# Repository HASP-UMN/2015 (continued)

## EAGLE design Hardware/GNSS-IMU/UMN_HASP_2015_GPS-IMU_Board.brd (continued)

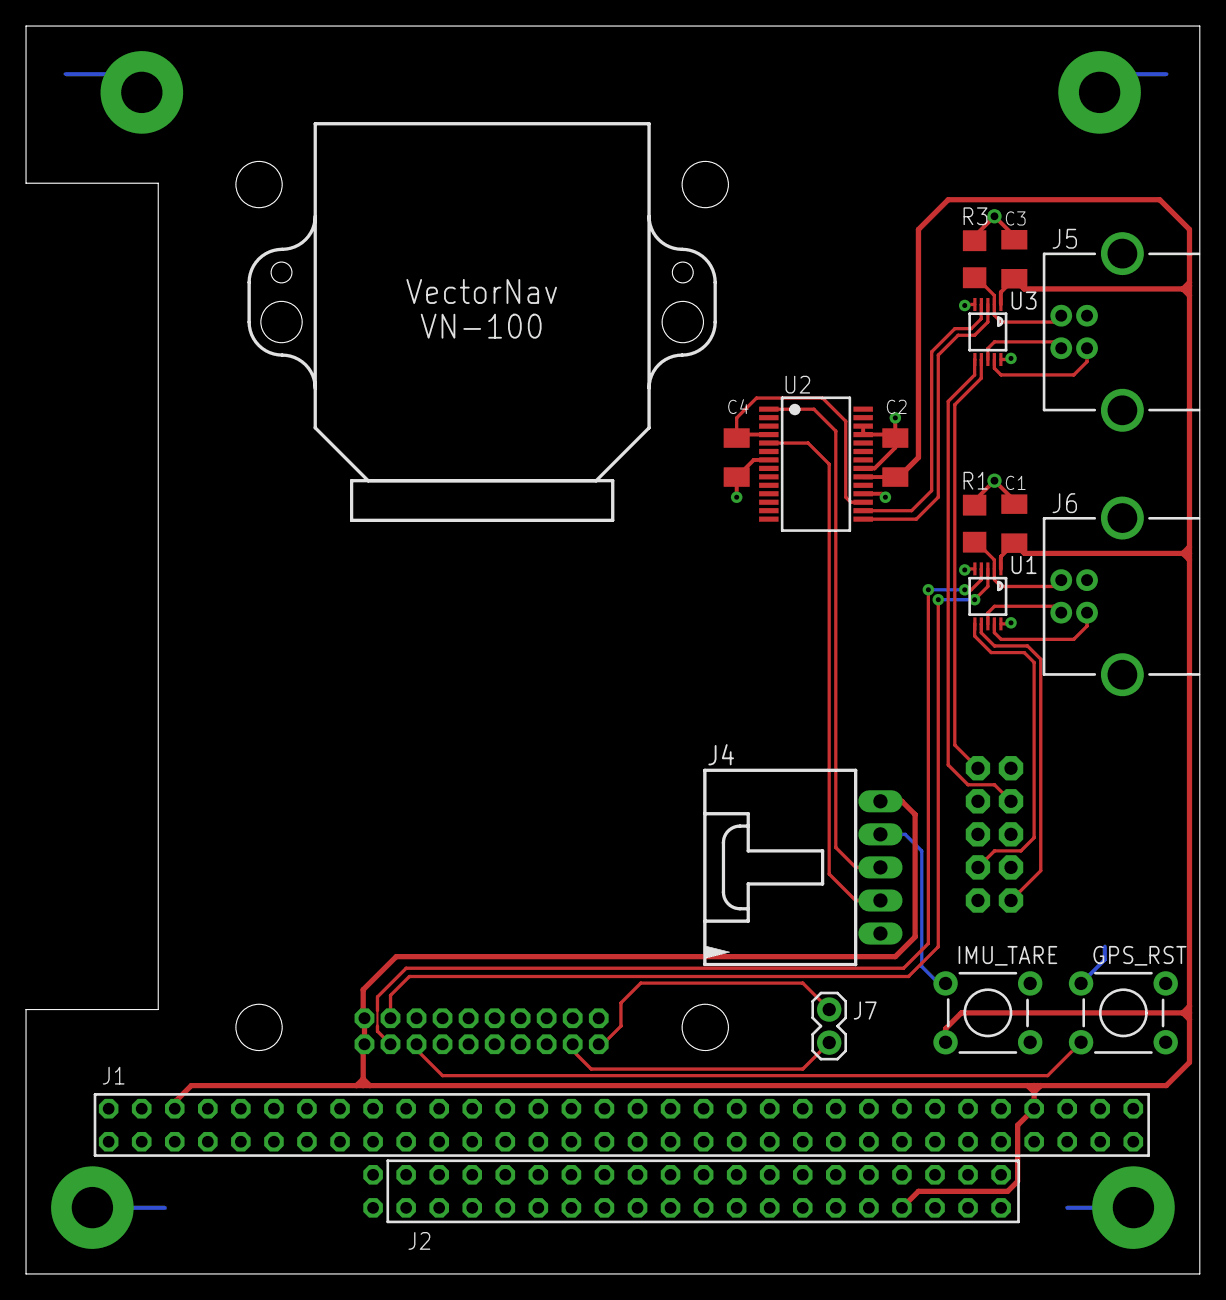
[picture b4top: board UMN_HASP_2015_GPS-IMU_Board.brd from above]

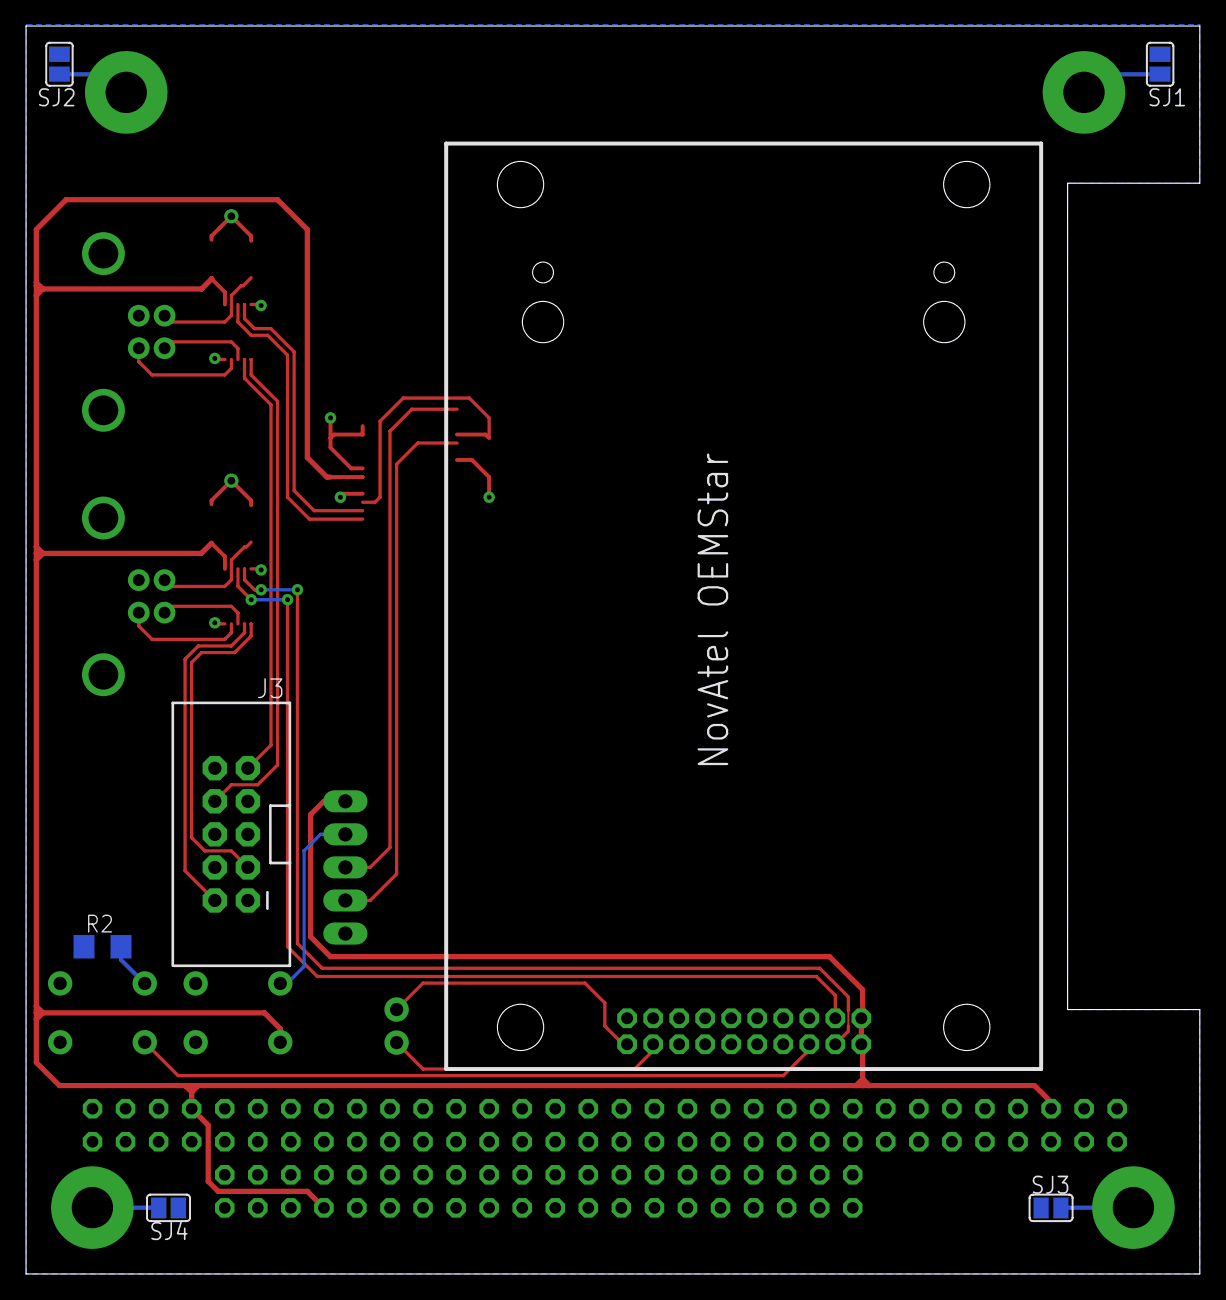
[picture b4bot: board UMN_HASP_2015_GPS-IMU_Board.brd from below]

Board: 2 copper layers, 90.2 x 95.9 mm, 24 parts (6 on the bottom side), 28 nets.

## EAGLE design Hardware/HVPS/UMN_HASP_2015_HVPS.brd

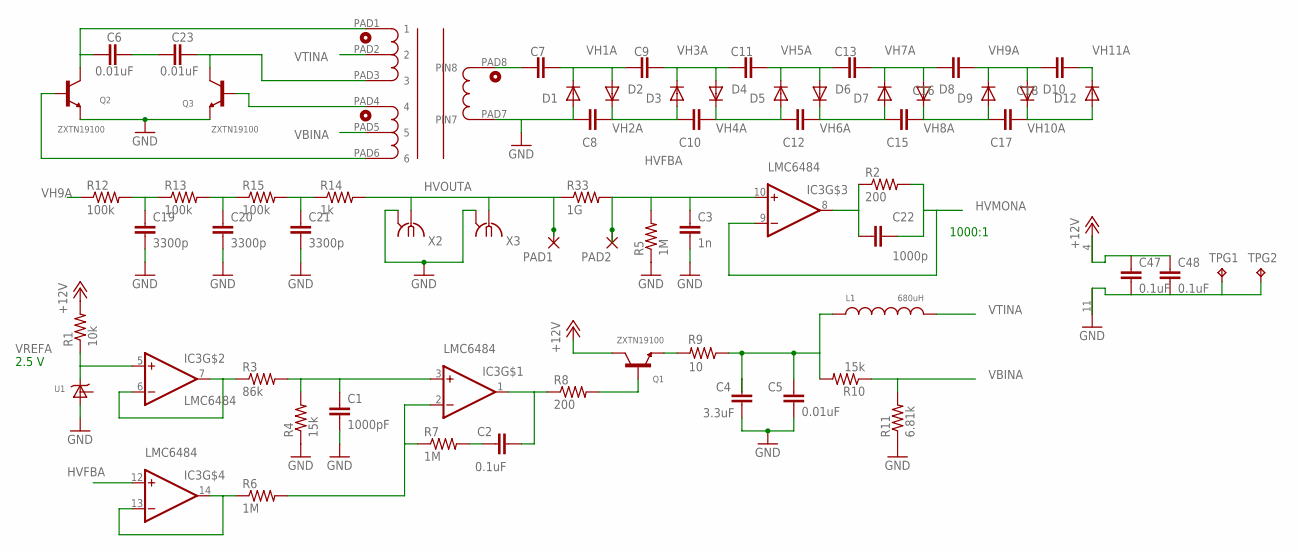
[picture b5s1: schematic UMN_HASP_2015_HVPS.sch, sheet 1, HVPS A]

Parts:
C1: 1000pF; C0603
C2, C47, C48: 0.1uF; C0603
C3: 1n; C0603
C4: 3.3uF; C0603
C5, C6, C23: 0.01uF; C0603
C7, C8, C9, C10, C11, C12, C13, C15, C16, C17, C18: C-EUC1206K; C1206K
C19, C20, C21: 3300p; C1206
C22: 1000p; C0603
D1, D2, D3, D4, D5, D6, D7, D8, D9, D10, D12: DIODE-DO-214AC; DO-214AC
IC3: LMC6484; SO14
L1: 680uH; INDUCTOR_SRR1280BOURNS
PAD1, PAD2: WIREPADSMD1,27-254; SMD1,27-2,54
Q1, Q2, Q3: ZXTN19100; SOT23_2CM_SQ_AREA
R1: 10k; R0603
R2, R8: 200; R0603
R3: 86k; R0603
R4, R10: 15k; R0603
R5, R6, R7: 1M; R0603
R9: 10; R2010
R11: 6.81k; R0603
R12, R13, R15: 100k; R0603
R14: 1k; R0603
R33: 1G; R2512
TPG1, TPG2: TPB1,27; B1,27
U1: ADR525; SOT23A
U$1: TDK_TRANSFORMER_RM6_CORE; SM_DCOILFORMER_RM6
X2, X3: BU-SMA-V-REVB; BU-SMA-V

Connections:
+12V: C47.1, C48.1, IC3.4 (V+), Q1.C, R1.2; also elsewhere on the board
GND: C1.2, C3.2, C4.2, C5.2, C8.1, C19.2, C20.2, C21.2, C47.2, C48.2, D1.A, IC3.11 (V-), Q2.E, Q3.E, R4.1, R5.1, R11.1, TPG1.TP, TPG2.TP, U1.2 (V-), U$1.PAD7 (PIN7), X2.2 (GND), X2.3 (GND), X2.4 (GND), X2.5 (GND), X3.2 (GND), X3.3 (GND), X3.4 (GND), X3.5 (GND); also elsewhere on the board
HVFBA: C3.1, IC3.10 (+IN), IC3.12 (+IN), PAD2.1, R5.2, R33.2
HVMONA: C22.1, IC3.9 (-IN), R2.2
HVOUTA: PAD1.1, R14.2, R33.1, X2.1, X3.1
unnamed: C22.2, IC3.8 (OUT), R2.1
unnamed: IC3.6 (-IN), IC3.7 (OUT), R3.1
unnamed: C1.1, IC3.3 (+IN), R3.2, R4.2
unnamed: C6.1, C23.2
unnamed: IC3.13 (-IN), IC3.14 (OUT), R6.1
unnamed: IC3.2 (-IN), R6.2, R7.1
unnamed: C6.2, Q2.C, U$1.PAD1 (1)
unnamed: C2.1, R7.2
unnamed: C2.2, IC3.1 (OUT), R8.1
unnamed: C4.1, C5.1, L1.P$1, R9.1, R10.2
unnamed: C7.1, U$1.PAD8 (PIN8)
unnamed: C23.1, Q3.C, U$1.PAD3 (3)
unnamed: C19.1, R12.2, R13.1
unnamed: C20.1, R13.2, R15.1
unnamed: C21.1, R14.1, R15.2
unnamed: Q1.E, R9.2
unnamed: Q1.B, R8.2
unnamed: Q3.B, U$1.PAD4 (4)
unnamed: Q2.B, U$1.PAD6 (6)
VBINA: R10.1, R11.2, U$1.PAD5 (5)
VH1A: C7.2, C9.1, D1.C, D2.A
VH2A: C8.2, C10.1, D2.C, D3.A
VH3A: C9.2, C11.1, D3.C, D4.A
VH4A: C10.2, C12.1, D4.C, D5.A
VH5A: C11.2, C13.1, D5.C, D6.A
VH6A: C12.2, C15.1, D6.C, D7.A
VH7A: C13.2, C16.1, D7.C, D8.A
VH8A: C15.2, C17.1, D8.C, D9.A
VH9A: C16.2, C18.1, D9.C, D10.A, R12.1
VH10A: C17.2, D10.C, D12.A
VH11A: C18.2, D12.C
VREFA: IC3.5 (+IN), R1.1, U1.1 (V+)
VTINA: L1.P$2, U$1.PAD2 (2)

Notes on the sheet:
2.5 V
1000:1

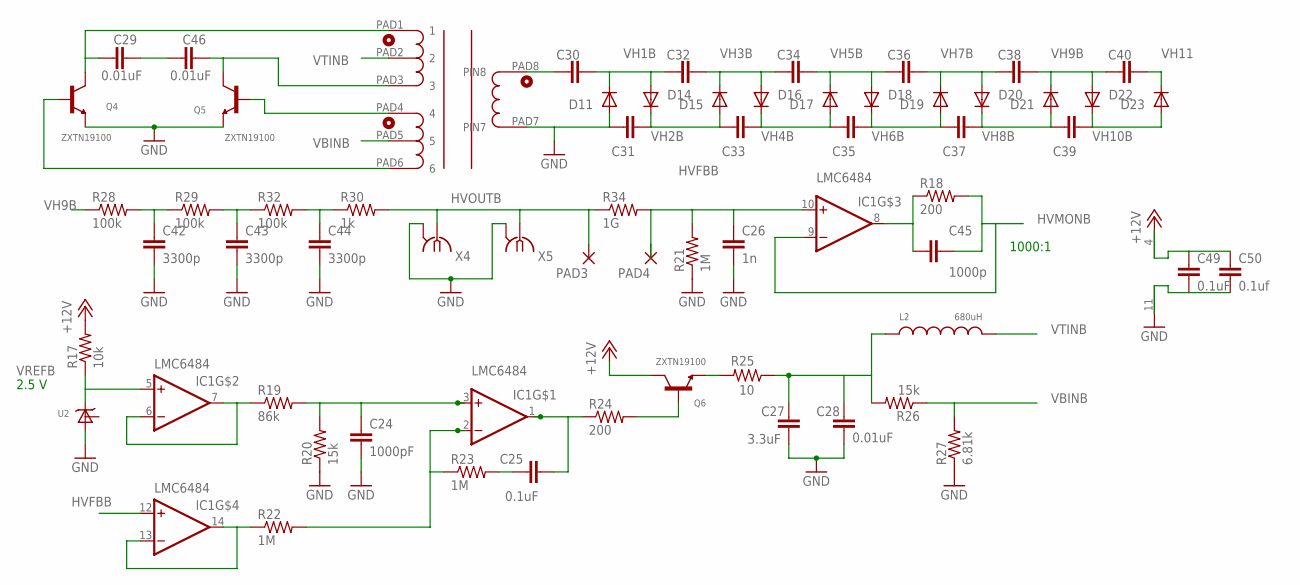
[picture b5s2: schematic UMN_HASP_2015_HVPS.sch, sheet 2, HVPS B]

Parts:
C24: 1000pF; C0603
C25, C49: 0.1uF; C0603
C26: 1n; C0603
C27: 3.3uF; C0603
C28, C29, C46: 0.01uF; C0603
C30, C31, C32, C33, C34, C35, C36, C37, C38, C39, C40: C-EUC1206K; C1206K
C42, C43, C44: 3300p; C1206
C45: 1000p; C0603
C50: 0.1uf; C0603
D11, D14, D15, D16, D17, D18, D19, D20, D21, D22, D23: DIODE-DO-214AC; DO-214AC
IC1: LMC6484; SO14
L2: 680uH; INDUCTOR_SRR1280BOURNS
PAD3, PAD4: WIREPADSMD1,27-254; SMD1,27-2,54
Q4, Q5, Q6: ZXTN19100; SOT23_2CM_SQ_AREA
R17: 10k; R0603
R18, R24: 200; R0603
R19: 86k; R0603
R20, R26: 15k; R0603
R21, R22, R23: 1M; R0603
R25: 10; R2010
R27: 6.81k; R0603
R28, R29, R32: 100k; R0603
R30: 1k; R0603
R34: 1G; R2512
U2: ADR525; SOT23A
U$2: TDK_TRANSFORMER_RM6_CORE; SM_DCOILFORMER_RM6
X4, X5: BU-SMA-V-REVB; BU-SMA-V

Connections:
+12V: C49.1, C50.1, IC1.4 (V+), Q6.C, R17.2; also elsewhere on the board
GND: C24.2, C26.2, C27.2, C28.2, C31.1, C42.2, C43.2, C44.2, C49.2, C50.2, D11.A, IC1.11 (V-), Q4.E, Q5.E, R20.1, R21.1, R27.1, U2.2 (V-), U$2.PAD7 (PIN7), X4.2 (GND), X4.3 (GND), X4.4 (GND), X4.5 (GND), X5.2 (GND), X5.3 (GND), X5.4 (GND), X5.5 (GND); also elsewhere on the board
HVFBB: C26.1, IC1.10 (+IN), IC1.12 (+IN), PAD4.1, R21.2, R34.2
HVMONB: C45.1, IC1.9 (-IN), R18.2
HVOUTB: PAD3.1, R30.2, R34.1, X4.1, X5.1
unnamed: IC1.6 (-IN), IC1.7 (OUT), R19.1
unnamed: C24.1, IC1.3 (+IN), R19.2, R20.2
unnamed: IC1.13 (-IN), IC1.14 (OUT), R22.1
unnamed: IC1.2 (-IN), R22.2, R23.1
unnamed: C25.1, R23.2
unnamed: C25.2, IC1.1 (OUT), R24.1
unnamed: C27.1, C28.1, L2.P$1, R25.1, R26.2
unnamed: Q6.E, R25.2
unnamed: Q6.B, R24.2
unnamed: C29.2, Q4.C, U$2.PAD1 (1)
unnamed: Q5.B, U$2.PAD4 (4)
unnamed: Q4.B, U$2.PAD6 (6)
unnamed: C30.1, U$2.PAD8 (PIN8)
unnamed: C42.1, R28.2, R29.1
unnamed: C43.1, R29.2, R32.1
unnamed: C44.1, R30.1, R32.2
unnamed: C45.2, IC1.8 (OUT), R18.1
unnamed: C29.1, C46.2
unnamed: C46.1, Q5.C, U$2.PAD3 (3)
VBINB: R26.1, R27.2, U$2.PAD5 (5)
VH1B: C30.2, C32.1, D11.C, D14.A
VH2B: C31.2, C33.1, D14.C, D15.A
VH3B: C32.2, C34.1, D15.C, D16.A
VH4B: C33.2, C35.1, D16.C, D17.A
VH5B: C34.2, C36.1, D17.C, D18.A
VH6B: C35.2, C37.1, D18.C, D19.A
VH7B: C36.2, C38.1, D19.C, D20.A
VH8B: C37.2, C39.1, D20.C, D21.A
VH9B: C38.2, C40.1, D21.C, D22.A, R28.1
VH10B: C39.2, D22.C, D23.A
VH11: C40.2, D23.C
VREFB: IC1.5 (+IN), R17.1, U2.1 (V+)
VTINB: L2.P$2, U$2.PAD2 (2)

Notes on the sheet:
2.5 V
1000:1

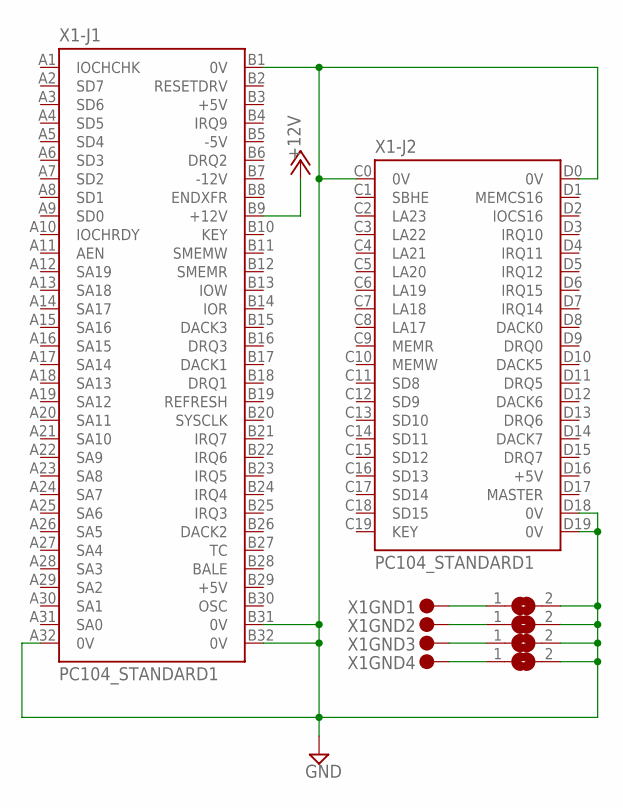
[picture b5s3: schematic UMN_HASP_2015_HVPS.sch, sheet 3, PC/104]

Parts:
SJ1, SJ2, SJ3, SJ4: SJ
X1: PC104_STANDARD1; PC104-STANDARD

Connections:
+12V: X1.B9 (+12V); also elsewhere on the board
GND: SJ1.2, SJ2.2, SJ3.2, SJ4.2, X1.A32 (0V), X1.B1 (0V), X1.B31 (0V), X1.B32 (0V), X1.C0 (0V), X1.D0 (0V), X1.D18 (0V), X1.D19 (0V); also elsewhere on the board
unnamed: SJ1.1, X1.GND@1 (1)
unnamed: SJ2.1, X1.GND@2 (1)
unnamed: SJ3.1, X1.GND@3 (1)
unnamed: SJ4.1, X1.GND@4 (1)

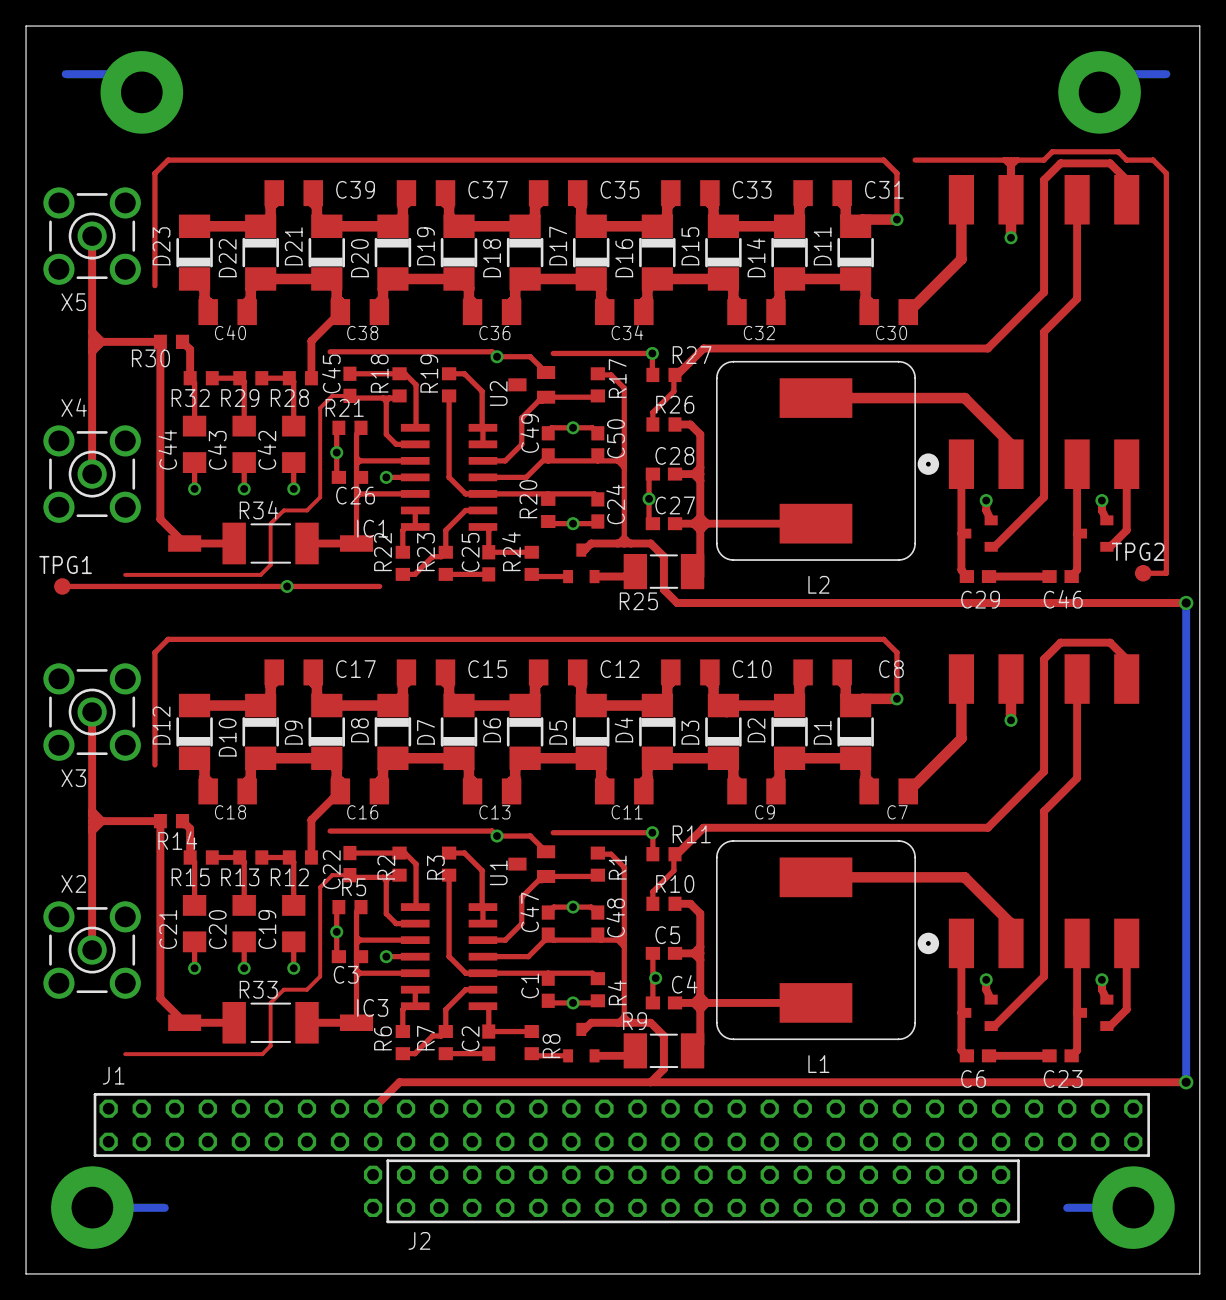
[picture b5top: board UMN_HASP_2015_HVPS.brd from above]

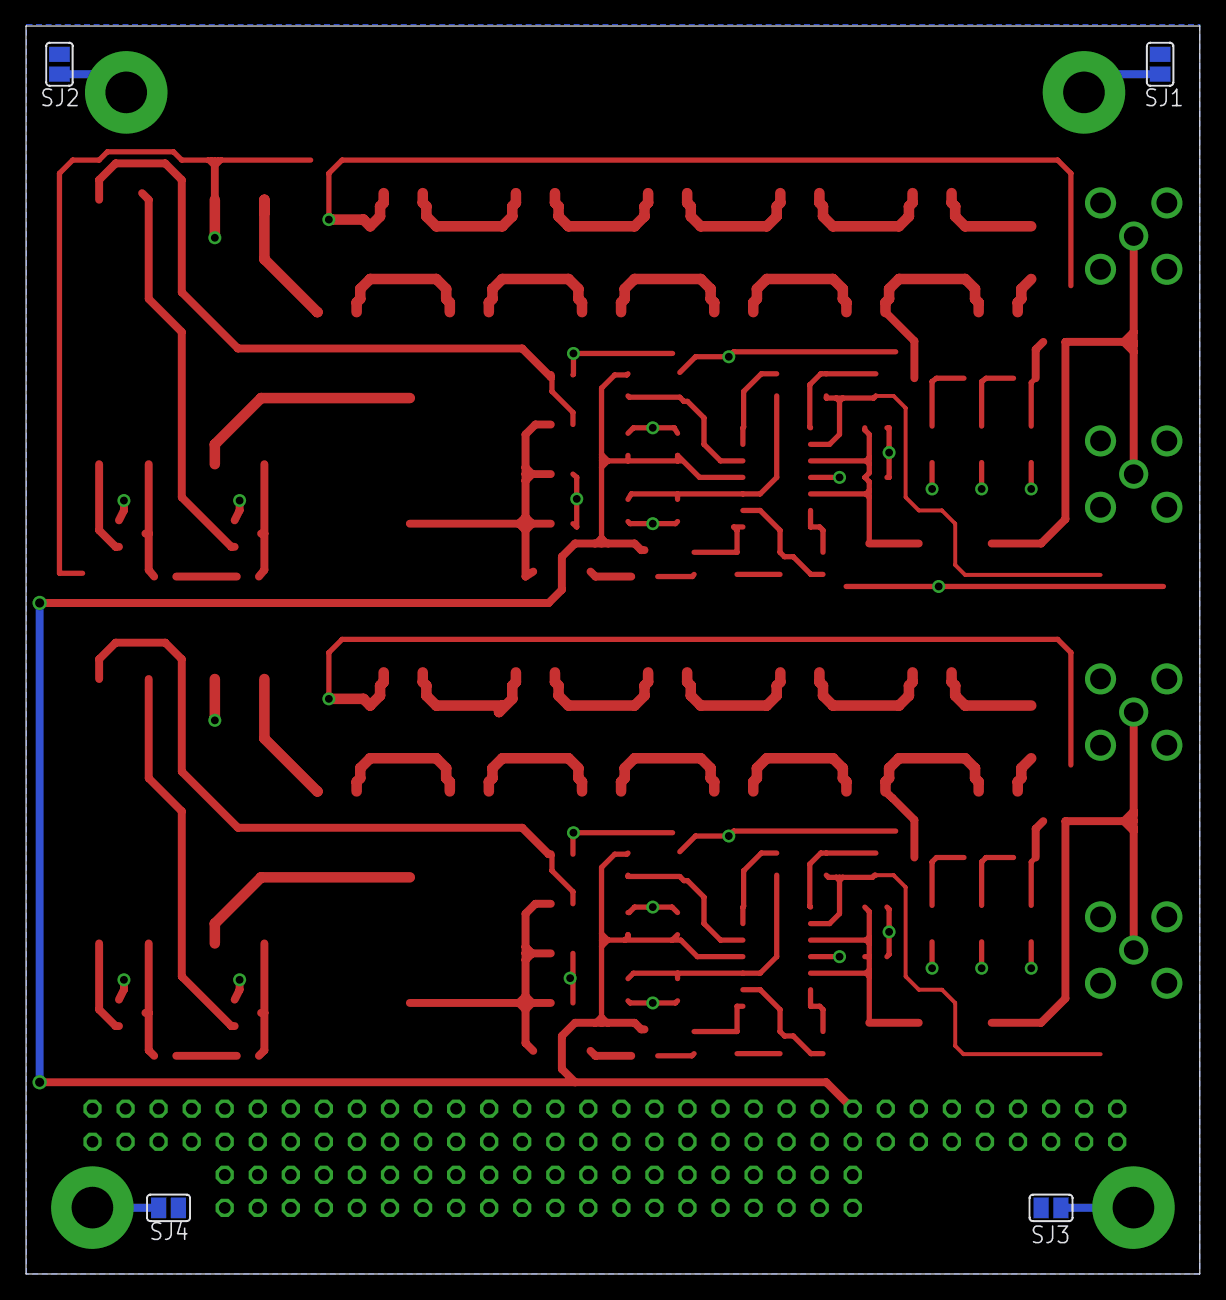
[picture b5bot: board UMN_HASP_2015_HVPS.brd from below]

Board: 2 copper layers, 90.2 x 95.9 mm, 131 parts (4 on the bottom side), 78 nets.

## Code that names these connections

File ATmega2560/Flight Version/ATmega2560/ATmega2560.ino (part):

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#define MANUAL_READ_ADDR 0x04 // 7-bit address for manual mode read register

// Peak threshhold discriminators. INT[7-4] on the ATmega2560 (inputs).
#define DISCRIMINATOR1 7 // INT7: Channel 1 discrimintor.
#define DISCRIMINATOR2 6 // INT6: Channel 2 discrimintor.
#define DISCRIMINATOR3 5 // INT5: Channel 3 discrimintor.
#define DISCRIMINATOR4 4 // INT4: Channel 4 discrimintor.

  // Port masks for Port H
#define ADC_CS   0B01000000
#define PK_RST1  0B00100000
#define PK_RST2  0B00010000
#define PK_RST3  0B00001000
#define PK_RST4  0B00000100
#define PK_RST_DEASSERT 0B01000011

//register uint8_t ADC_CS_ASSERT asm("r18");
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//#define ADC_CS_ASSERT 0B00000011
//#define ADC_CS_DEASSERT 0B01000011

#define FIFO_RST 0B00000010
#define FIFO_WR  0B00000001
#define FIFO_WR_ASSERT 0B01000010   //see PORTH on eagle file: FIFO_WR active low
#define FIFO_WR_DEASSERT 0B01000011

unsigned int checksum = 0;
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  // Initialize the digital outputs on Port F to low. PORTF is the register for the state of the outputs.
  PORTF = B00000000;
 
  // PORT K (FIFO full flag on PK1)
  DDRK   = DDRK   & ~B00000010;    // Set PK1 as input
  PORTK  = PORTK  |  B00000010;    // Activate PULL UP resistor
  PCMSK1 = PCMSK1 |  B00000010;    // Enable PCINT17 on PK1
  PCICR  = PCICR  | (1<<PCIE2);    // Activate interrupt on enabled PCINT23-16
 
  // PORT E (CH[1-4] threshhold discriminators)
  DDRE  = DDRE  & ~B11110000;  /* Set PE7 (DISCRIMINATOR1) as input */
  PORTE = PORTE & ~B11110000;  /* Activate PULL DOWN resistors */
  EICRB = B11111111; // Set INT[4-7] to be on their rising edges
  EIMSK = B11110000; // Enable INT[4-7] 
  
  // PORT D (GPS_PPS as Input)
  DDRD = DDRD | B00000000;         // Sets PD3 as input
  EICRA = B11000000;               // Set INT3 to be rising edge
  EIMSK = EIMSK | B00001000;       // Enables INT[3]
   
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   
  // Reset the FIFO.
  PORTH |= FIFO_WR; // set FIFO_WR high before resetting
  PORTH &= ~FIFO_RST; // Toggle FIFO_RST pin from HIGH to LOW
  PORTH = PORTH |  FIFO_RST; // Toggle FIFO_RST pin from LOW to HIGH  

  // Write A/D configuration register to enable internal Vref and temperature sensor 
  PORTH = PORTH & ~ADC_CS; // Toggle ADC_CS LOW
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    data.tempRaw += SPI.transfer(0);
    PORTH |= ADC_CS; // Toggle ADC_CS HIGH

    // Reset the peak detector. PH3 (the 4th bit of Port H) is the CH3 reset signal.
    PORTH = PORTH | data.reset; // Toggle PK_RST3 HIGH
    PORTH = PORTH & ~data.reset; // Toggle PK_RST3 LOW
    return data;       
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
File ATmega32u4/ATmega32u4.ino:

#define HALF_FULL_INT 1  // this is the interrupt number, comes from FIFO
#define FIFO_READ_ENABLE B00100000// to FIFO, PF5
#define OUTPUT_ENABLE B00000001// to tri state buffer, PF0
#define BALE_INT 0 // this is the interrupt number, comes from Tomcat
#define IOR B01000000// from Tomcat, PC6
#define ADDR_VALID_IOR B11000000 // from decoder/Tomcat, PC7
#define IRQ_OUT B00000010 // to tomcat, PF1

#define IOCHRDY B00010000 // to tomcat, PF4
#define IOCHRDY_READ_OUTPUT_ENABLE  B00000010
#define IOCHRDY_READ_HIGH           B00110010
#define IOCHRDY_READ_OUTPUT_DISABLE B00110001
#define BUFFER_DISABLE

#define IRQ_LOW_ENABLE  B00110000  // OE active, IRQ, IOCHRDY, FIFO_RD, inactive
#define IRQ_HIGH_ENABLE B00110010 // IRQ, OE active; IOCHRDY, FIFO_RD inactive
//#define IRQ_LOW_DISABLE B00110001 // IRQ, OE, IOCHRDY, FIFO_RD inactive. 
#define IRQ_HIGH_DISABLE  B00110001

volatile unsigned int HF_count = 0;
volatile unsigned int bale_count = 0;
volatile unsigned int av_count = 0;

void half_full_handler(){
  
//  PORTF = PORTF | IRQ_OUT & ~OUTPUT_ENABLE;// turning OUTPUT_ENABLE low here as well so irq gets through buffer
////  HF_count++;  
//  PORTF = PORTF & ~IRQ_OUT | OUTPUT_ENABLE; 
  PORTF = IRQ_LOW_ENABLE;  //Pulling IRQ low and opening buffer because tomcat holds irqs high by default even though they're active high
  PORTF = IRQ_HIGH_ENABLE; 
  PORTF = IRQ_HIGH_DISABLE;
// we have to leave the irq high because it's high by default and if we lower it it will go high when the buffer is tristated, causing a false interrupt
 // HF_count++;
  
}

void bale_handler(){
  
  //if ( (PINC & ADDR_VALID_IOR) == B10000000){ // think IOR is active low from tomcat
  if (PINC == B10000000){
    PORTF = B00000010;    //IOCHRDY low, read_enable low, output_enable low, irq high (default high)
    PORTF = B00110010;    //IOCHRDY high, read_enable high, output_enable low, irq high
    PORTF = B00110011;                     //IOCHRDY high, read_enable high, output_enable high, irq high
 //   av_count++;   
  }
//  bale_count++;
  
}

void setup() {
  DDRF = IRQ_OUT | OUTPUT_ENABLE | FIFO_READ_ENABLE | IOCHRDY;  //set pins to output mode
  PORTF = PORTF | FIFO_READ_ENABLE | IOCHRDY | OUTPUT_ENABLE; // setting read_enable high initially; this is a requirement so that the FIFO can be reset correctly by atmega2560
  DDRC = B00000000; // all inputs, only using 6 and 7
  // also setting IOCHRDY high by default, it is active low
  // also setting OUTPUT_ENABLE high (off) initially so tomcat can correctly start up
  delay(120000);
  attachInterrupt(HALF_FULL_INT, half_full_handler, FALLING); // this line is active low from FIFO 
  attachInterrupt(BALE_INT, bale_handler, RISING);  
//  Serial.begin(115200); Serial.flush();
//  Serial.println("Starting");
}

void loop() {
// just waiting for interrupts
//  Serial.print("HF: "); Serial.println(HF_count);
// // Serial.print("Bale: "); Serial.println(bale_count);
//  Serial.print("AV: "); Serial.println(av_count);
//  delay(500);

}

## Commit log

2015-06-17 Josiah's first commit - copies of 2014 code
2015-06-17 Filled telemtry string with tildes
2015-06-17 Removed simple_gpio files
2015-06-17 Renamed downlink to telemetry
2015-06-17 Removed sensorData struct, cleaned up globaldefs.h
2015-06-17 arons first commit
2015-06-17 Cleanup of globaldefs
2015-06-17 updating
2015-06-17 Further edit of globaldefs file
2015-06-17 Edit of globaldefs to reflect telemetry.c + edit of telemetry.c
2015-06-17 Removed main copy.c
2015-06-17 Removed .DS_Store
2015-06-17 first draft of irq driver
2015-06-17 Edited GPS software
2015-06-17 Removed gps_novatel copies
2015-06-18 Adding VN100.c/h to read the imu and serial.c/h to read from serial devices.
2015-06-18 files from tomcat working with imu
2015-06-18 Modified VN100 files to write to imu struct. General Cleanup
2015-06-19 VN100 changes
2015-06-19 Modified main.c to pass read_VN100() the imu struct.
2015-06-19 VN100 modifications
2015-06-19 Moved six detector declarations from globaldefs.h to main.c so that globaldefs.h could be referenced in multiple files without having multiple declaration problems.
2015-06-19 Aaron's changes globaldefs.h setup and calling fork() in main().
2015-06-22 FT232RL BREAKOUT BOARD
2015-06-22 Adding board/schematic files for HAXDT hardware
2015-06-22 Summer schedule + PSIP
2015-06-22 Moved FT232R-Breakout_v37/ to Hardware/ directory
2015-06-22 Adding board/schematics for HAXDT hardware
2015-06-22 System Tests
2015-06-22 got rid of .DS_Store's
2015-06-22 got rid of updateEventCounter copy.c
2015-06-23 FT232 folder ----> GNSS-IMU folder
2015-06-23 -rename
2015-06-23 Subsystem tests
2015-06-23 EAGLE file cleanup
2015-06-23 datasheets
2015-06-26 PC/104 board screenshots
2015-06-29 added /modules and driver
2015-06-29 updated main.c
2015-06-29 deleted some useless files
2015-06-29 Need to define ATmega2560 I/O pins
2015-06-30 added ATmega32u4 code draft
2015-06-30 updated ATmega32u4 code draft
2015-06-30 updated ATmega32u4 code
2015-07-01 updated ATmega code
2015-07-01 ATmega2560 firmware (prelim)
2015-07-02 ATmega2560 firmware
2015-07-02 improved ATmega32u4 code
2015-07-03 Bitmasking bug is corrected, PORT 7 is working
2015-07-03 disabled pSig
2015-07-03 updated atmega32u4
2015-07-03 added FIFO FF
2015-07-03 Files for GPS
2015-07-06 More work on gps code. Detector code is commented out in main loop due to testing of gps. Small cosmetic changes to other files.
2015-07-07 updating atmega 2560
2015-07-08 Edits..DO NOT RUN, IS NOT COMPLETE
2015-07-09 Worked on logging GPS data. In main.c, code for ISA bus still commented out for testing GPS and IMU.
2015-07-09 port manip.
2015-07-10 Improvements to gps_novatel. Addition of errorword to handles errors and to build an error word to be used in telemetry. errorword is still a work in progress.
2015-07-10 removed simple_gpio since it is not used by the gps this year.
2015-07-11 Latest version; revert to digitalWrite(). Not yet functional on CH3. May use PORTH method, but need to test trigger threshhold with greater ease
2015-07-13 Refined errorword.c and added error reporting to gps_novatel.c
2015-07-13 Created utility to read from binary GPS data file and print pertinent data to the screen. Intended for testing of the gps.
2015-07-14 Improved errorword.c so it is now fully functional, improved gps_novatel to report errors more thoroughly. Set up VN100.c to report errors. Set up telemetry.c.
2015-07-15 Latest
2015-07-15 Refined IMU code.
2015-07-15 Reorganized GPS Utilities
2015-07-16 Added error checking to the opening of the IMU data file.
2015-07-16 Reprioritized errors
2015-07-20 ATmega2560 port stuff
2015-07-20 ATmega2560 interrupt config
2015-07-20 updating atmega code
2015-07-20 added atmega2560.h
2015-07-20 added debugging to atmega2560
2015-07-20 atmega2560
2015-07-20 added Timing
    added timing to ATmega2560.ino
2015-07-20 Latest working
2015-07-21 2560 update
2015-07-21 32u4 update
2015-07-21 update 2560
2015-07-21 test fifo write
2015-07-21 channel 1&3 still acting funny "3805" pk val
2015-07-21 Added Timing to Main code
    Not implemented in loops or data yet, but setting up base timing
    structure.
2015-07-21 added .h for DS3231 RTC
2015-07-23 added IOCHRDY to 32u4
2015-07-23 updated DS3231.h
2015-07-24 timing changes
    square wave interrupts are causing problems.
2015-07-24 timing
2015-07-25 debugging 2560
2015-07-25 2560
2015-07-25 Timing update with micros() and added RTC Setting .ino
2015-07-25 debugging fifo
2015-07-25 Added Testing Debugging commands
2015-07-27 Hardware notes
2015-07-27 32u4 flight code -- needs testing
2015-07-27 2560 flight
2015-07-27 Tweaked code when loading code onto Tomcat after OS reinstall.
2015-07-27 Hamming checksum
2015-07-27 Checksum function
2015-07-27 update 32u4
2015-07-27 Combined All Tomcat code/modules into one folder.
2015-07-27 Updated "Tomcat code" folder to "Tomcat" for cmd line ease.
2015-07-28 Added Start Time offset for RTC
2015-07-28 fixed logic error in timing setup
2015-07-28 Timing complete, not checked, updated other functions: see description notes.
    * added TIMING.h for all time declarations
    * Edited newEventCHx for time
    * added uSecStamp and TicStamp for each event
    * changed checksum passing to add both new variables instead of
    milliseconds
    * changed send_data to reflect new variables
2015-07-28 IRQ line change from 6 to 5.
2015-07-28 Modified make file to have read_fifo program compile automatically.
2015-07-28 README.md
2015-07-28 README.md in the main directory
2015-07-28 Timing init and first packet data checked OK
2015-07-29 uptodate 32u4
2015-07-29 Added ambient temp code to TIMING.h
2015-07-29 Updated Setup delay()
2015-07-29 Updated packet size per Seth's email, did not combine startbyte and channel yet
2015-07-30 updated send_data
2015-07-30 Added timestamp to IMU based on time in GPS packets.
2015-07-30 Created AMTEL project for 32U4
    Using Atmel Studio to compile assembly level code for 32U4 chip to
    alleviate timing issues.
2015-07-31 latest 2560 and atmel 32u4 code
2015-07-31 Latest 2560 and 32U4 Codes
2015-07-31 updated checksum
2015-07-31 Adding pipes for error reporting. Still in progress.
2015-08-01 2560 optimization in send_data()
2015-08-01 Added and tested named pipes to send error between two processes. Updated Error Reporting.
2015-08-01 Updated 2560 code
2015-08-03 Updated 2560. Fixed checksum.
2015-08-03 commenting out fprintf(s) for flight
2015-08-03 updated 32u4 to handle rejected irqs
2015-08-04 Updated path for datafiles.
2015-08-04 Files updated to support communication (named pipes) between processes.
2015-08-04 Updated Error Enumeration.
2015-08-04 driver
2015-08-04 added write control of irq enabling to driver
2015-08-04 removed most debug serialprints.
2015-08-04 removed debugging serial prints
2015-08-04 Final Flight Update
2015-08-04 Final Flight Update
    Commented out all Serial Print data
2015-08-05 Updated gps code from 8/4/15
2015-08-05 commented out reset channel counts
2015-08-06 Latest flight code on Tomcat
2015-08-12 GPS util output redirect to file
2015-08-13 Redirected console to file
2015-10-27 Fixed bug in clock sync. function + removed unneeded delay from ISRs
2015-10-27 Folder cleanup
2015-10-29 flight version
2015-11-02 git rm .DS_Store --cached
